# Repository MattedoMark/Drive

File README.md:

# Battle Bot
Battle_Bot_Mind - This is for the brain of the battle bot which will contol both the all wheel drive and the vertical spinner.
NOTE: All other files are part files for SolidWorks

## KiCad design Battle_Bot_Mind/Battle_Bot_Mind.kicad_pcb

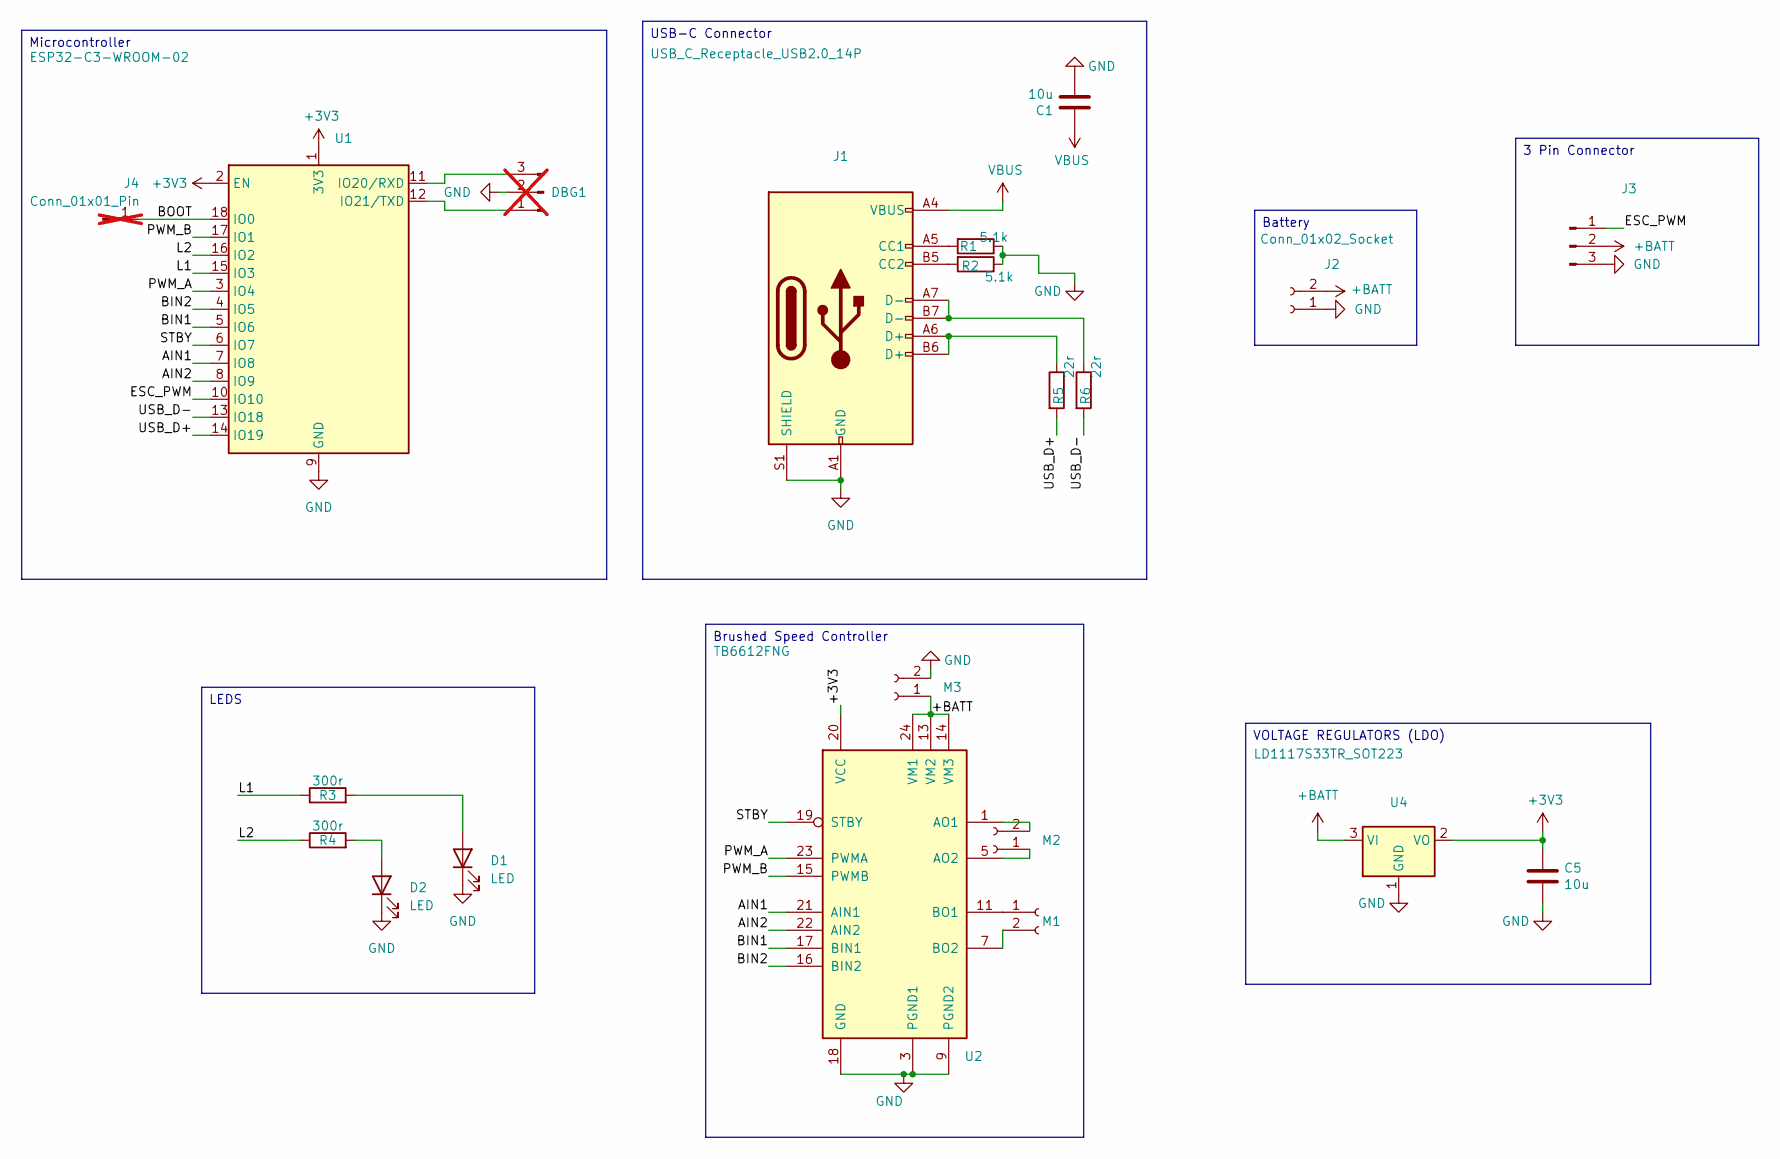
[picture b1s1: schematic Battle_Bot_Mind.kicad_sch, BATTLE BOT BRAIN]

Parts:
C1, C5: 10u; C_0805_2012Metric; LCSC C408141
D1, D2: LED; LED_0402_1005Metric; LCSC C965793
DBG1: Conn_01x03_Pin; PinHeader_1x03_P2.00mm_Vertical; not fitted
J1: USB_C_Receptacle_USB2.0_14P; USB_C_Receptacle_HRO_TYPE-C-31-M-12; LCSC C165948
J2: Conn_01x02_Socket; AMASS_XT30U-F_1x02_P5.0mm_Vertical; LCSC C428721
J3: Conn_01x03_Pin; PinHeader_1x03_P2.00mm_Vertical
J4: Conn_01x01_Pin; PinSocket_1x01_P2.54mm_Vertical; not fitted
M1, M2, M3: Conn_01x02_Socket; PinHeader_1x02_P2.54mm_Vertical
R1, R2: 5.1k; R_0402_1005Metric_Pad0.72x0.64mm_HandSolder; LCSC C105872
R3, R4: 300r; R_0402_1005Metric; LCSC C25102
R5, R6: 22r; R_0402_1005Metric_Pad0.72x0.64mm_HandSolder; LCSC C105872
U1: ESP32-C3-WROOM-02; LCSC C2944070
U2: TB6612FNG; SSOP-24_5.3x8.2mm_P0.65mm; LCSC C141517
U4: LD1117S33TR_SOT223; SOT-223-3_TabPin2; LCSC C86781

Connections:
+3V3: C5.1, U1.1 (3V3), U1.2 (EN), U2.20 (VCC), U4.2 (VO)
+BATT: J2.2, J3.2, M3.1, U2.13 (VM2), U2.14 (VM3), U2.24 (VM1), U4.3 (VI); also elsewhere on the board
/AIN1: U1.7 (IO8), U2.21 (AIN1)
/AIN2: U1.8 (IO9), U2.22 (AIN2)
/BIN1: U1.5 (IO6), U2.17 (BIN1)
/BIN2: U1.4 (IO5), U2.16 (BIN2)
/BOOT: J4.1, U1.18 (IO0)
/ESC_PWM: J3.1, U1.10 (IO10)
/L1: R3.1, U1.15 (IO3)
/L2: R4.1, U1.16 (IO2)
/PWM_A: U1.3 (IO4), U2.23 (PWMA)
/PWM_B: U1.17 (IO1), U2.15 (PWMB)
/STBY: U1.6 (IO7), U2.19 (STBY)
/USB_D+: R5.2, U1.14 (IO19)
/USB_D-: R6.2, U1.13 (IO18)
GND: C1.2, C5.2, D1.1 (K), D2.1 (K), DBG1.2, J1.A1 (GND), J1.A12 (GND), J1.B1 (GND), J1.B12 (GND), J1.S1 (SHIELD), J2.1, J3.3, M3.2, R1.1, R2.1, U1.9 (GND), U1.19 (GND), U2.3 (PGND1), U2.4 (PGND1), U2.9 (PGND2), U2.10 (PGND2), U2.18 (GND), U4.1 (GND); also elsewhere on the board
unnamed: D1.2 (A), R3.2
unnamed: D2.2 (A), R4.2
unnamed: DBG1.1, U1.12 (IO21/TXD)
unnamed: DBG1.3, U1.11 (IO20/RXD)
unnamed: J1.A5 (CC1), R1.2
unnamed: J1.B5 (CC2), R2.2
unnamed: J1.A6 (D+), J1.B6 (D+), R5.1
unnamed: J1.A7 (D-), J1.B7 (D-), R6.1
unnamed: M1.1, U2.11 (BO1), U2.12 (BO1)
unnamed: M1.2, U2.7 (BO2), U2.8 (BO2)
unnamed: M2.1, U2.5 (AO2), U2.6 (AO2)
unnamed: M2.2, U2.1 (AO1), U2.2 (AO1)
VBUS: C1.1, J1.A4 (VBUS), J1.A9 (VBUS), J1.B4 (VBUS), J1.B9 (VBUS)

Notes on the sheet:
USB-C Connector
Microcontroller
Battery
Brushed Speed Controller
VOLTAGE REGULATORS (LDO)
3 Pin Connector
LEDS

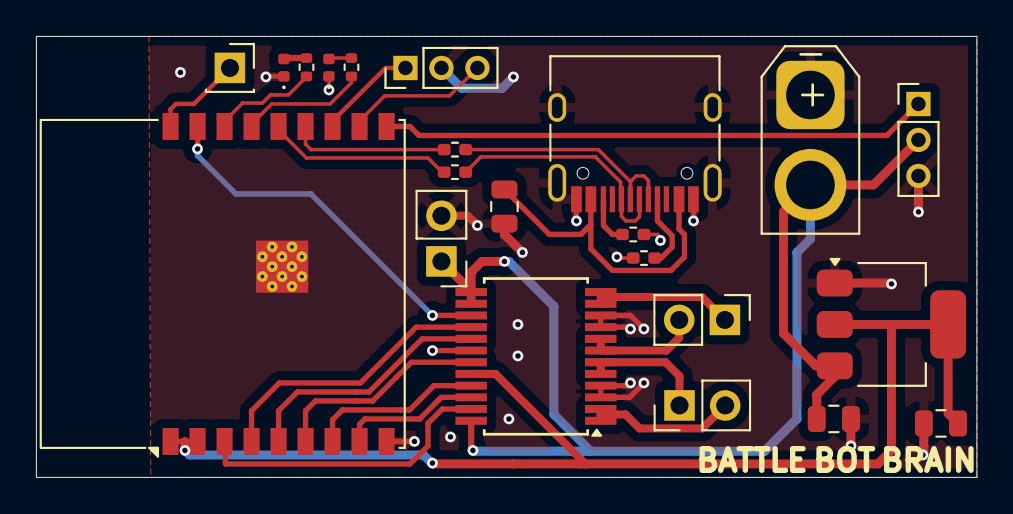
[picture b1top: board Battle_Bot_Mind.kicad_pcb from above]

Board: 2 copper layers, 52.2 x 24.5 mm, 22 parts (0 on the bottom side), 29 nets.

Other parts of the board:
C6: 2.2u; C_0805_2012Metric

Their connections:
+BATT: C6.1; also elsewhere on the board
GND: C6.2; also elsewhere on the board

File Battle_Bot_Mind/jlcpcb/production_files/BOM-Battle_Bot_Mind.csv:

Comment,Designator,Footprint,LCSC,Quantity
5.1k,"R1,R2,R5,R6",R_0402_1005Metric_Pad0.72x0.64mm_HandSolder,C105872,4
TB6612FNG,U2,SSOP-24_5.3x8.2mm_P0.65mm,C141517,1
USB_C_Receptacle_USB2.0_14P,J1,USB_C_Receptacle_HRO_TYPE-C-31-M-12,C165948,1
300r,"R3,R4",R_0402_1005Metric,C25102,2
ESP32-C3-WROOM-02,U1,ESP32-C3-WROOM-02,C2944070,1
10u,"C1,C5",C_0805_2012Metric,C408141,2
Conn_01x02_Socket,J2,AMASS_XT30U-F_1x02_P5.0mm_Vertical,C428721,1
LD1117S33TR_SOT223,U4,SOT-223-3_TabPin2,C86781,1
LED,"D1,D2",LED_0402_1005Metric,C965793,2
Conn_01x02_Socket,M2,PinHeader_1x02_P2.54mm_Vertical,,1
Conn_01x02_Socket,M1,PinHeader_1x02_P2.54mm_Vertical,,1
2.2u,C6,C_0805_2012Metric,,1
Conn_01x03_Pin,J3,PinHeader_1x03_P2.00mm_Vertical,,1
Conn_01x02_Socket,M3,PinHeader_1x02_P2.54mm_Vertical,,1

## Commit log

2025-07-20 work
2025-07-20 README.md
2025-07-28 ISAAC_CHANGED_STUFF
2025-07-29 isaac
2025-08-07 jlc2
